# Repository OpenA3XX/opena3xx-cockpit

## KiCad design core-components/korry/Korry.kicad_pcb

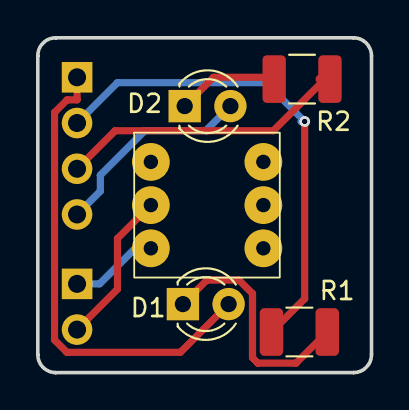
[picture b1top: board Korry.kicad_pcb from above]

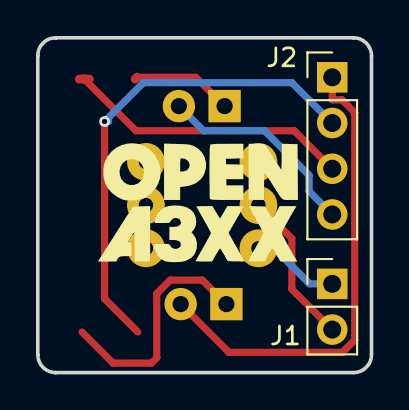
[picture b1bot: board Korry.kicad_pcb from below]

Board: 2 copper layers, 18.5 x 18.6 mm, 7 parts (2 on the bottom side), 8 nets.

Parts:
D1, D2: LED; LED_D3.0mm
J1: Conn_01x02_Pin; PinHeader_1x02_P2.54mm_Vertical
J2: Conn_01x04_Pin; PinHeader_1x04_P2.54mm_Vertical
R1, R2: R; R_1210_3225Metric_Pad1.30x2.65mm_HandSolder
U1: Korry_Switch_Discrete

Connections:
unnamed: D1.2 (A), J2.1
unnamed: D1.1 (K), R1.1
unnamed: D2.2 (A), J2.4
unnamed: D2.1 (K), R2.1
unnamed: J1.1, U1.1 (SW_COM)
unnamed: J1.2, U1.2 (SW1)
unnamed: J2.2, R1.2
unnamed: J2.3, R2.2

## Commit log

2026-01-25 Initial Commit
    Initial Commit
2026-01-25 Add initial project documentation and license
    Added CODE_OF_CONDUCT.md, CONTRIBUTING.md, LICENCE, and README.md to establish project guidelines, contribution instructions, licensing terms, and an overview of the OpenA3XX Airbus cockpit build pro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
2026-01-25 Add empty todo.txt files to project directories
    Created placeholder todo.txt files in glareshield, mip, and pedestal directories to track future tasks.
2026-02-22 Add 5mm LED footprints and KiCad settings
    Add multiple generated LED_THT:LED_D5.0mm footprints to the Korry footprint library (core-components/korry/Korry.kicad_pcb). Update project settings in OpenA3XX.kicad_pro with expanded design default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
2026-03-29 Korry V3
    Korry V3
2026-03-29 KorryUpdates
    KorryUpdates
2026-03-29 Updates
    Updates
